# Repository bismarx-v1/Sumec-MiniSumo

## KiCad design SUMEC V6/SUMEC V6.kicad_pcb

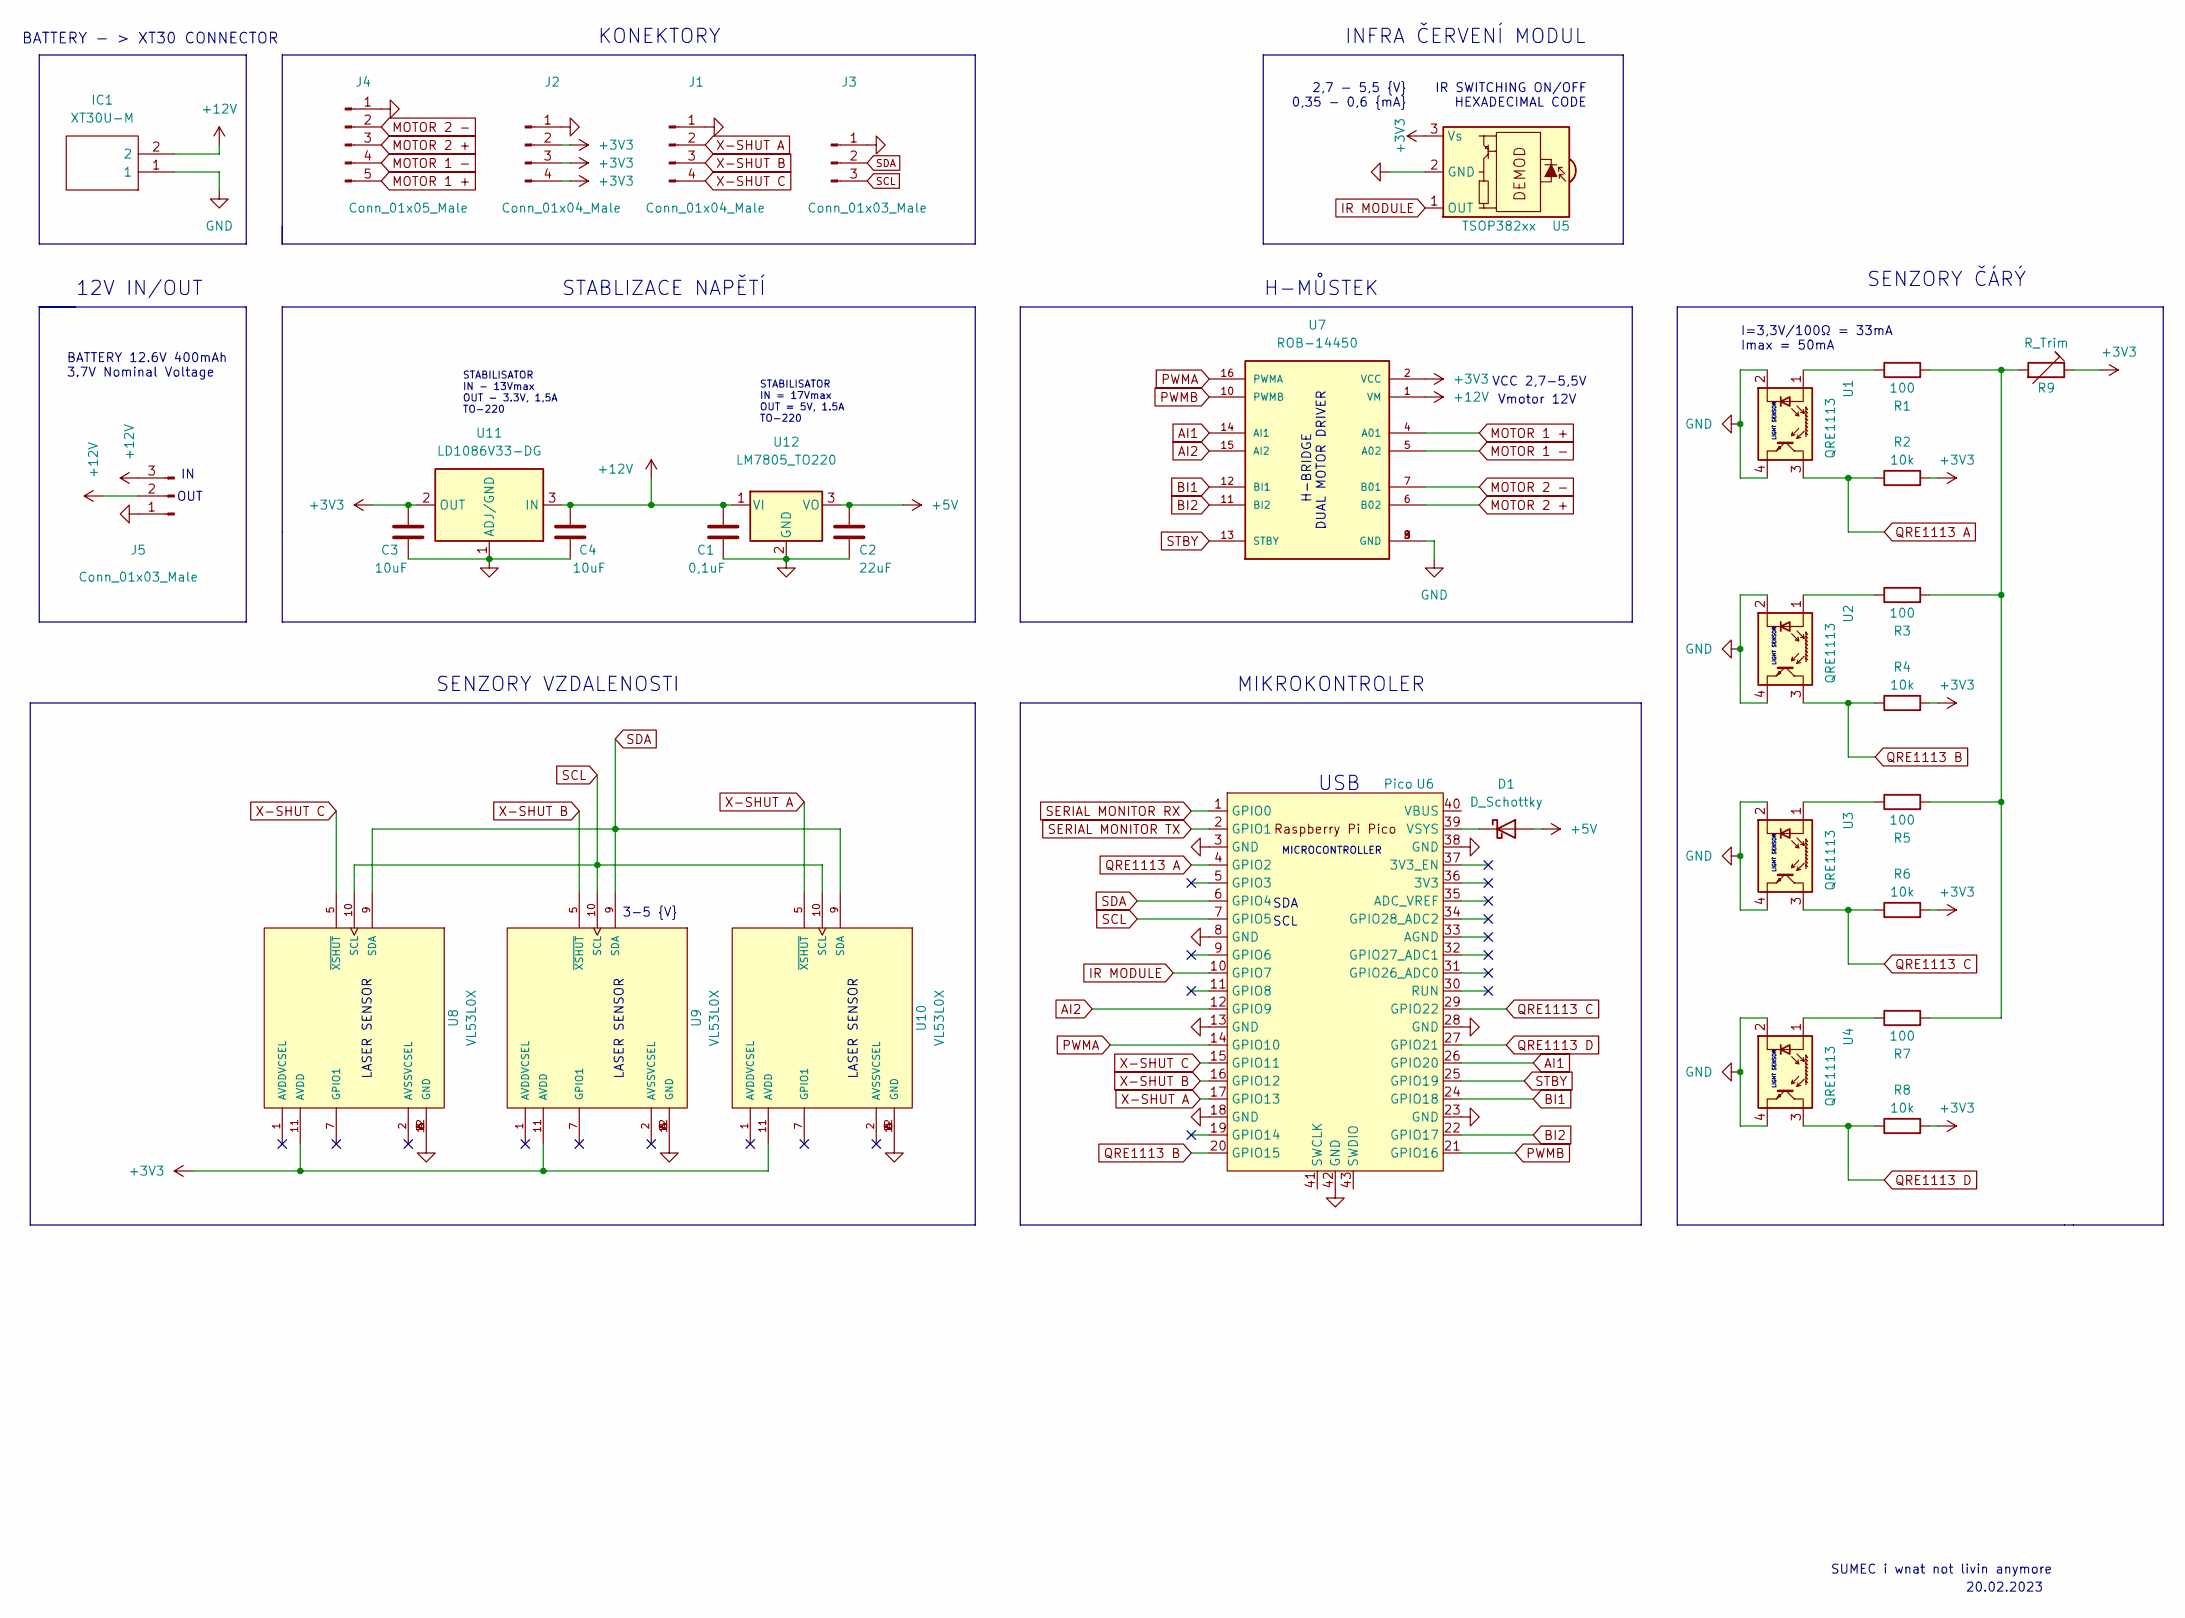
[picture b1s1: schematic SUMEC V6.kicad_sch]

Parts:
C1: 0,1uF; CP_Radial_D4.0mm_P2.00mm
C2: 22uF; CP_Radial_D4.0mm_P2.00mm
C3, C4: 10uF; CP_Radial_D4.0mm_P2.00mm
D1: D_Schottky; D_A-405_P2.54mm_Vertical_KathodeUp
IC1: XT30U-M; AMASS_XT30U-M_1x02_P5.0mm_Vertical; Manufacturer_Part_Number XT30U-M; LCSC C99101
J1, J2: Conn_01x04_Male; PinHeader_1x04_P2.54mm_Vertical
J3, J5: Conn_01x03_Male; PinHeader_1x03_P2.54mm_Vertical
J4: Conn_01x05_Male; PinHeader_1x05_P2.54mm_Vertical
R1, R3, R5, R7: 100; R_Axial_DIN0204_L3.6mm_D1.6mm_P1.90mm_Vertical
R2, R4, R6, R8: 10k; R_Axial_DIN0204_L3.6mm_D1.6mm_P1.90mm_Vertical
R9: R_Trim; Potentiometer_ACP_CA6-H2,5_Horizontal
U1, U2, U3, U4: QRE1113; OnSemi_CASE100AQ
U5: TSOP382xx; Vishay_MINICAST-3Pin
U6: Pico; RPi_Pico_SMD_TH
U7: ROB-14450; MODULE_ROB-14450; PARTREV 11-13-17
U8, U9, U10: VL53L0X; SENSOR_VL53L0X; PART_REV 1.0
U11: LD1086V33-DG; TO-220-3_Vertical
U12: LM7805_TO220; TO-220-3_Vertical

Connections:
+3V3: C3.1, J2.2, J2.3, J2.4, R2.2, R4.2, R6.2, R8.2, R9.1, U5.3 (Vs), U7.2 (VCC), U8.11 (AVDD), U9.11 (AVDD), U10.11 (AVDD), U11.2 (OUT)
+5V: C2.1, D1.2 (A), U12.3 (VO)
+12V: C1.1, C4.1, IC1.2, J5.2, J5.3, U7.1 (VM), U11.3 (IN), U12.1 (VI)
AI1: U6.26 (GPIO20), U7.14 (AI1)
AI2: U6.12 (GPIO9), U7.15 (AI2)
BI1: U6.24 (GPIO18), U7.12 (BI1)
BI2: U6.22 (GPIO17), U7.11 (BI2)
GND: C1.2, C2.2, C3.2, C4.2, IC1.1, J1.1, J2.1, J3.1, J4.1, J5.1, U1.2 (K), U1.4, U2.2 (K), U2.4, U3.2 (K), U3.4, U4.2 (K), U4.4, U5.2 (GND), U6.3 (GND), U6.8 (GND), U6.13 (GND), U6.18 (GND), U6.23 (GND), U6.28 (GND), U6.38 (GND), U6.42 (GND), U7.3 (GND), U7.8 (GND), U7.9 (GND), U8.3 (GND), U8.4 (GND), U8.6 (GND), U8.12 (GND), U9.3 (GND), U9.4 (GND), U9.6 (GND), U9.12 (GND), U10.3 (GND), U10.4 (GND), U10.6 (GND), U10.12 (GND), U11.1 (ADJ/GND), U12.2 (GND)
IR MODULE: U5.1 (OUT), U6.10 (GPIO7)
MOTOR 1 +: J4.5, U7.4 (A01)
MOTOR 1 -: J4.4, U7.5 (A02)
MOTOR 2 +: J4.3, U7.6 (B02)
MOTOR 2 -: J4.2, U7.7 (B01)
unnamed: D1.1 (K), U6.39 (VSYS)
unnamed: R1.1, U1.1 (A)
unnamed: R1.2, R3.2, R5.2, R7.2, R9.2
unnamed: R3.1, U2.1 (A)
unnamed: R5.1, U3.1 (A)
unnamed: R7.1, U4.1 (A)
PWMA: U6.14 (GPIO10), U7.16 (PWMA)
PWMB: U6.21 (GPIO16), U7.10 (PWMB)
QRE1113 A: R2.1, U1.3, U6.4 (GPIO2)
QRE1113 B: R4.1, U2.3, U6.20 (GPIO15)
QRE1113 C: R6.1, U3.3, U6.29 (GPIO22)
QRE1113 D: R8.1, U4.3, U6.27 (GPIO21)
SCL: J3.3, U6.7 (GPIO5), U8.10 (SCL), U9.10 (SCL), U10.10 (SCL)
SDA: J3.2, U6.6 (GPIO4), U8.9 (SDA), U9.9 (SDA), U10.9 (SDA)
SERIAL MONITOR RX: U6.1 (GPIO0)
SERIAL MONITOR TX: U6.2 (GPIO1)
STBY: U6.25 (GPIO19), U7.13 (STBY)
X-SHUT A: J1.2, U6.17 (GPIO13), U10.5 (~XSHUT)
X-SHUT B: J1.3, U6.16 (GPIO12), U9.5 (~XSHUT)
X-SHUT C: J1.4, U6.15 (GPIO11), U8.5 (~XSHUT)

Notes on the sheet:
3-5 {V}
H-MŮSTEK
OUT
LASER SENSOR
Vmotor 12V
SCL
STABILISATOR IN = 17Vmax OUT = 5V, 1.5A TO-220
MICROCONTROLLER
SUMEC i wnat not livin anymore
SENZORY ČÁRÝ
SDA
LIGHT SENSOR
VCC 2,7-5,5V
I=3,3V/100Ω = 33mA Imax = 50mA
STABILISATOR IN - 13Vmax OUT - 3.3V, 1,5A TO-220
MIKROKONTROLER
BATTERY - > XT30 CONNECTOR
SENZORY VZDALENOSTI
20.02.2023
2,7 - 5,5 {V} 0,35 - 0,6 {mA}
INFRA ČERVENÍ MODUL
IR SWITCHING ON/OFF HEXADECIMAL CODE
KONEKTORY
BATTERY 12.6V 400mAh 3.7V Nominal Voltage
USB
12V IN/OUT
H-BRIDGE DUAL MOTOR DRIVER
STABLIZACE NAPĚTÍ

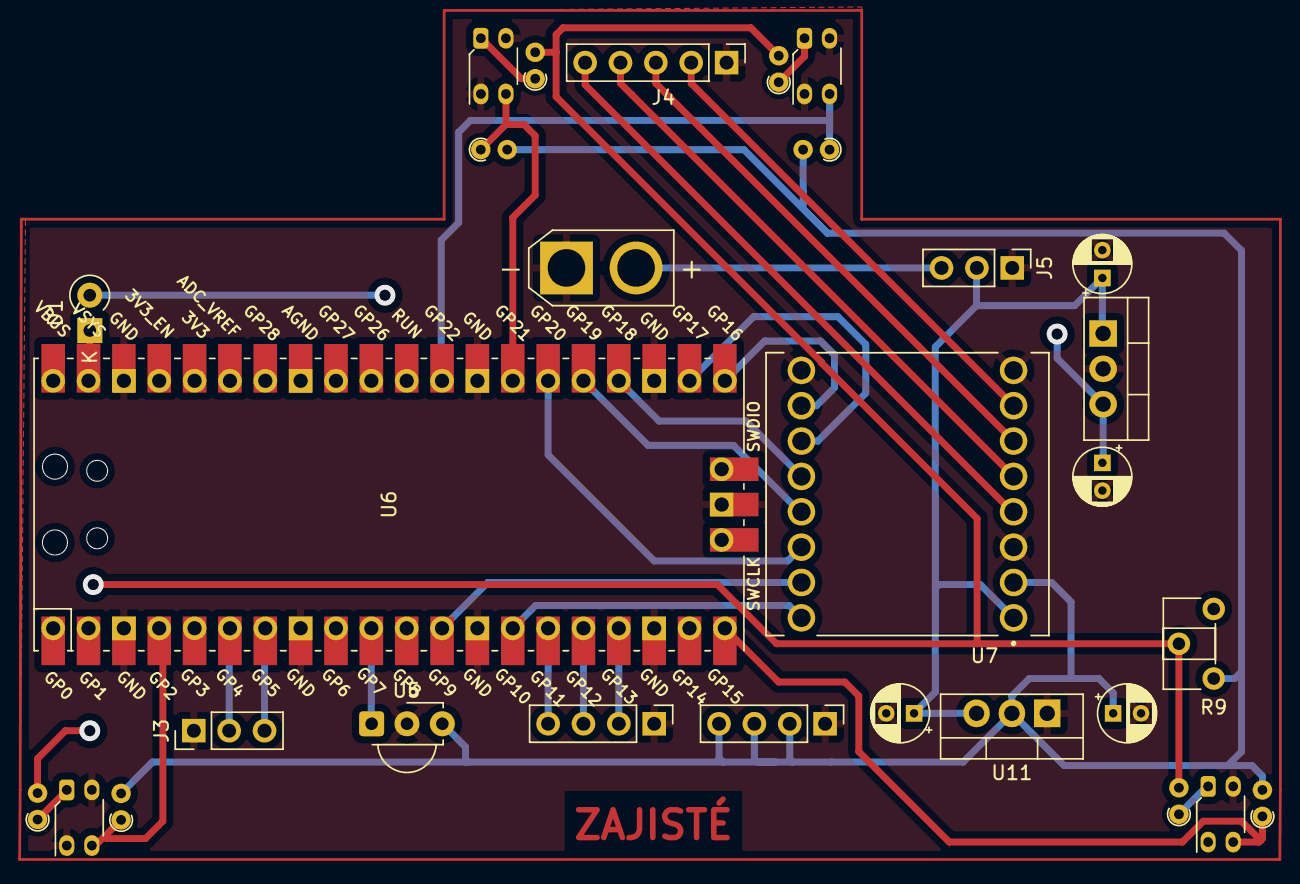
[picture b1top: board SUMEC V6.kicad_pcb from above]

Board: 2 copper layers, 29 parts (0 on the bottom side), 31 nets.
